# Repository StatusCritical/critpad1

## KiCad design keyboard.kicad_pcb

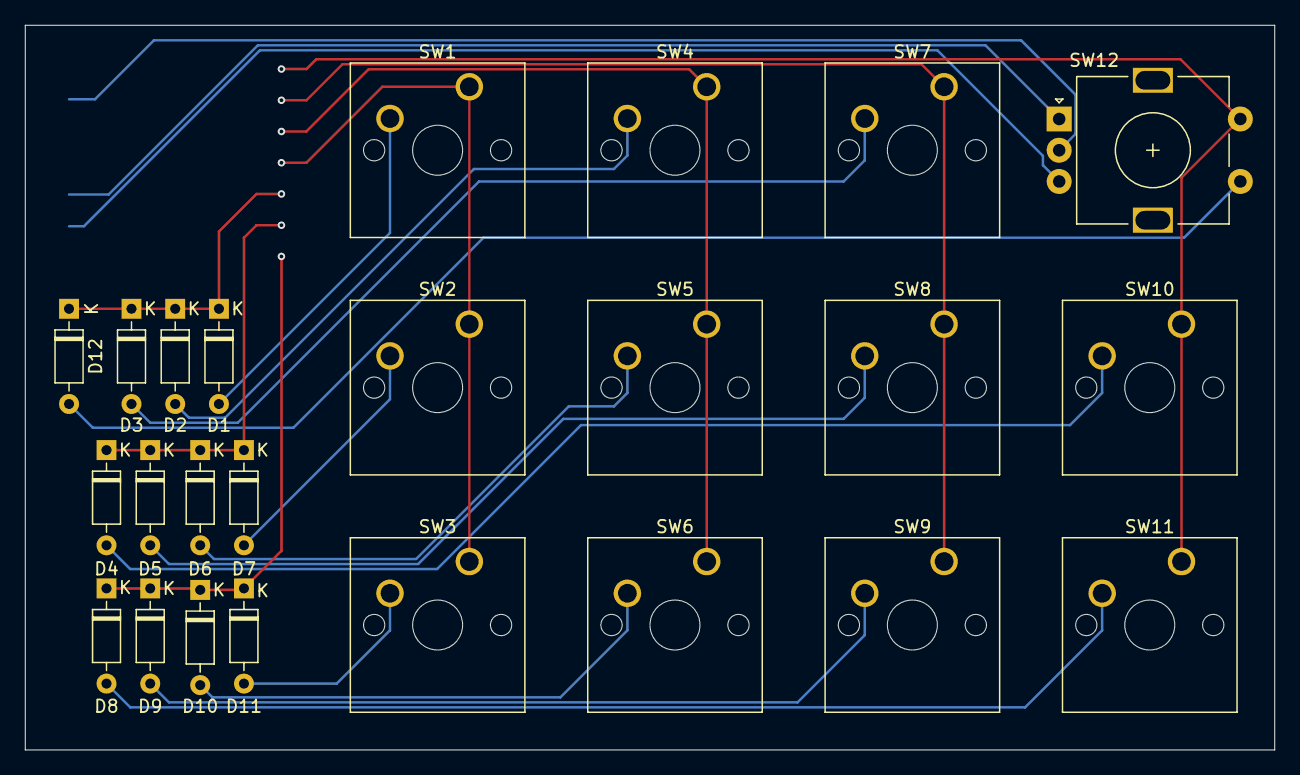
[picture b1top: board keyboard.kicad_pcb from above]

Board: 2 copper layers, 100.0 x 58.0 mm, 25 parts (1 on the bottom side), 22 nets.

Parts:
D1, D2, D3, D4, D5, D6, D7, D8, D9, D10, D11, D12: 1N4148; D_DO-35_SOD27_P7.62mm_Horizontal
SW1, SW2, SW3, SW4, SW5, SW6, SW7, SW8, SW9, SW10, SW11: SW_Push; SW_Cherry_MX_1.00u_PCB
SW12: RotaryEncoder_Switch; RotaryEncoder_Alps_EC11E-Switch_Vertical_H20mm
U1: Seeed Studio XIAO SAMD21; XIAO-SAMD21-RP2040-14P-2.54-21X17.8MM (Seeeduino XIAO)

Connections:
GND: SW12.C, U1.13 (GND)
unnamed: D1.2 (A), SW1.2
unnamed: D1.1 (K), D2.1 (K), D3.1 (K), D12.1 (K), U1.5 (PA8_A4_D4_SDA)
unnamed: D2.2 (A), SW4.2
unnamed: D3.2 (A), SW7.2
unnamed: D4.2 (A), SW10.2
unnamed: D4.1 (K), D5.1 (K), D6.1 (K), D7.1 (K), U1.6 (PA9_A5_D5_SCL)
unnamed: D5.2 (A), SW8.2
unnamed: D6.2 (A), SW5.2
unnamed: D7.2 (A), SW2.2
unnamed: D8.2 (A), SW11.2
unnamed: D9.2 (A), SW9.2
unnamed: D10.2 (A), SW6.2
unnamed: D8.1 (K), D9.1 (K), D10.1 (K), D11.1 (K), U1.7 (PB08_A6_D6_TX)
unnamed: D11.2 (A), SW3.2
unnamed: D12.2 (A), SW12.S1
unnamed: SW10.1, SW11.1, SW12.S2, U1.1 (PA02_A0_D0)
unnamed: SW7.1, SW8.1, SW9.1, U1.2 (PA4_A1_D1)
unnamed: SW12.A, U1.10 (PA5_A9_D9_MISO)
unnamed: SW12.B, U1.9 (PA7_A8_D8_SCK)
unnamed: SW4.1, SW5.1, SW6.1, U1.3 (PA10_A2_D2)
unnamed: SW1.1, SW2.1, SW3.1, U1.4 (PA11_A3_D3)

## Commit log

2024-10-09 finished v1
2024-10-10 rewired the rotary encoder into the matrix
2024-10-11 changed to a through hole microprocessor
